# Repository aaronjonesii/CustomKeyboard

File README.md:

# CustomKeyboard
 Full Custom Mechanical Keyboard

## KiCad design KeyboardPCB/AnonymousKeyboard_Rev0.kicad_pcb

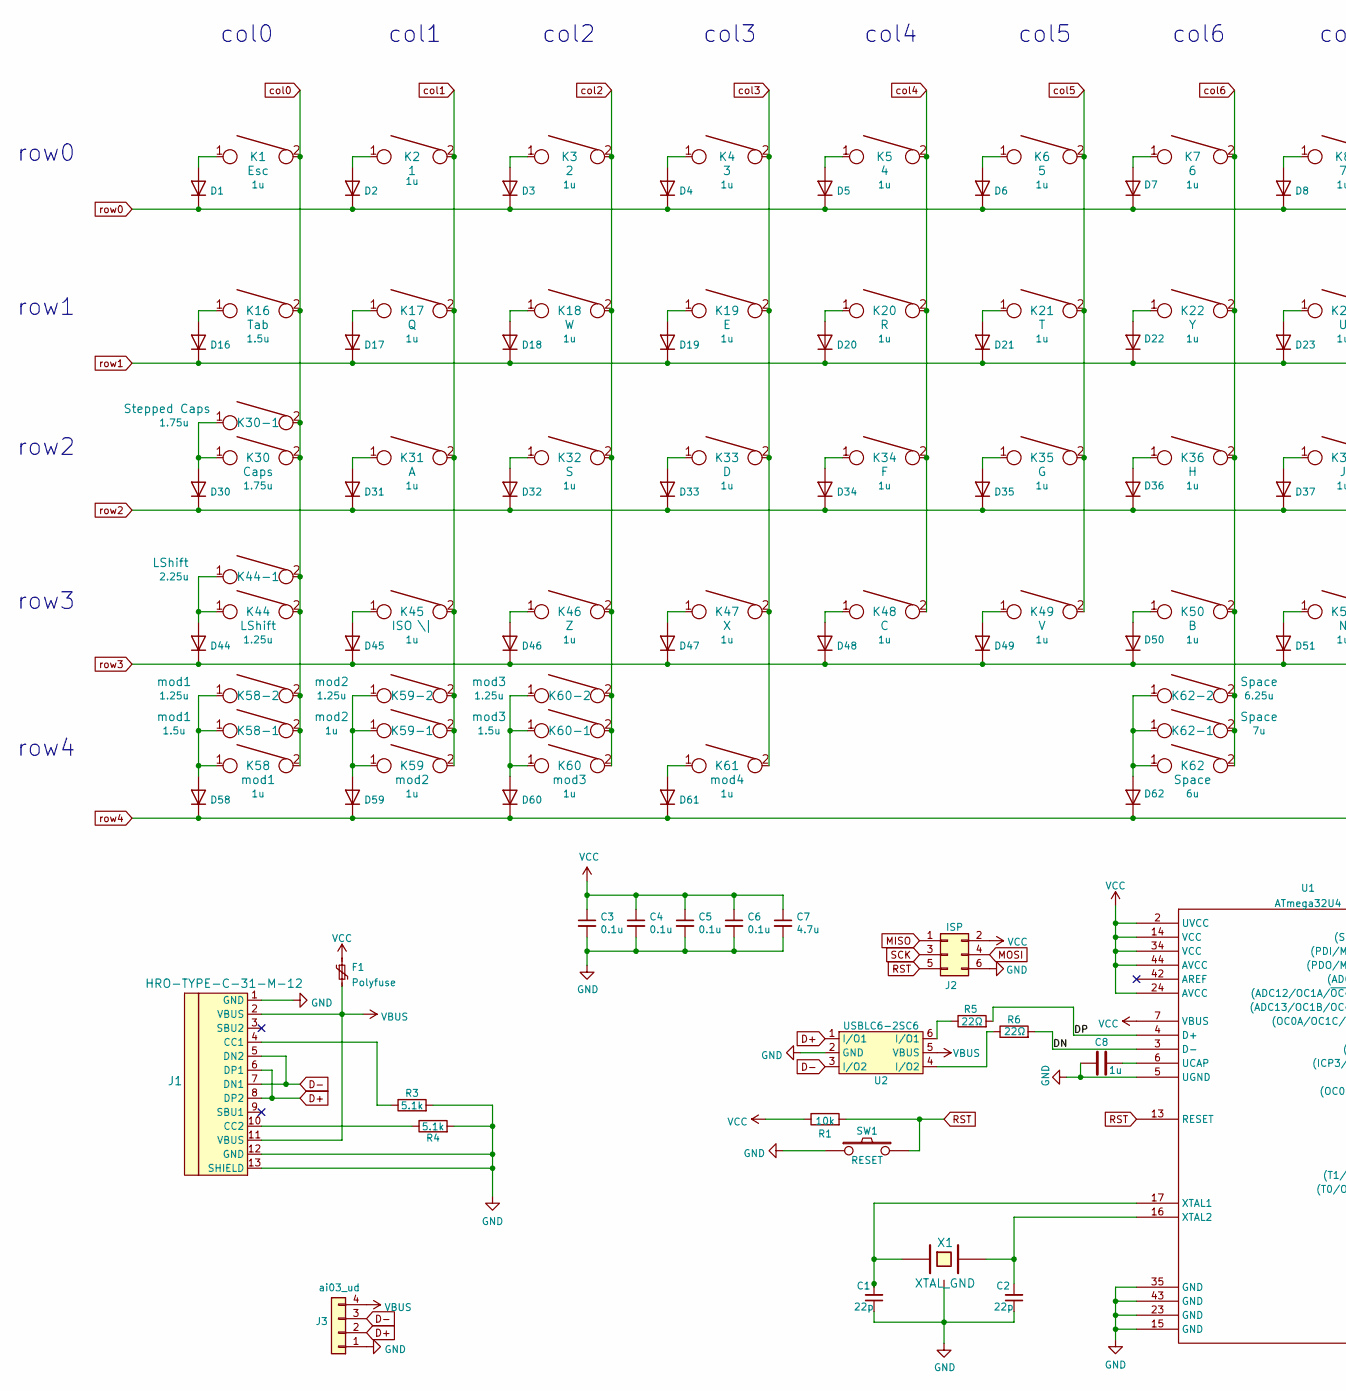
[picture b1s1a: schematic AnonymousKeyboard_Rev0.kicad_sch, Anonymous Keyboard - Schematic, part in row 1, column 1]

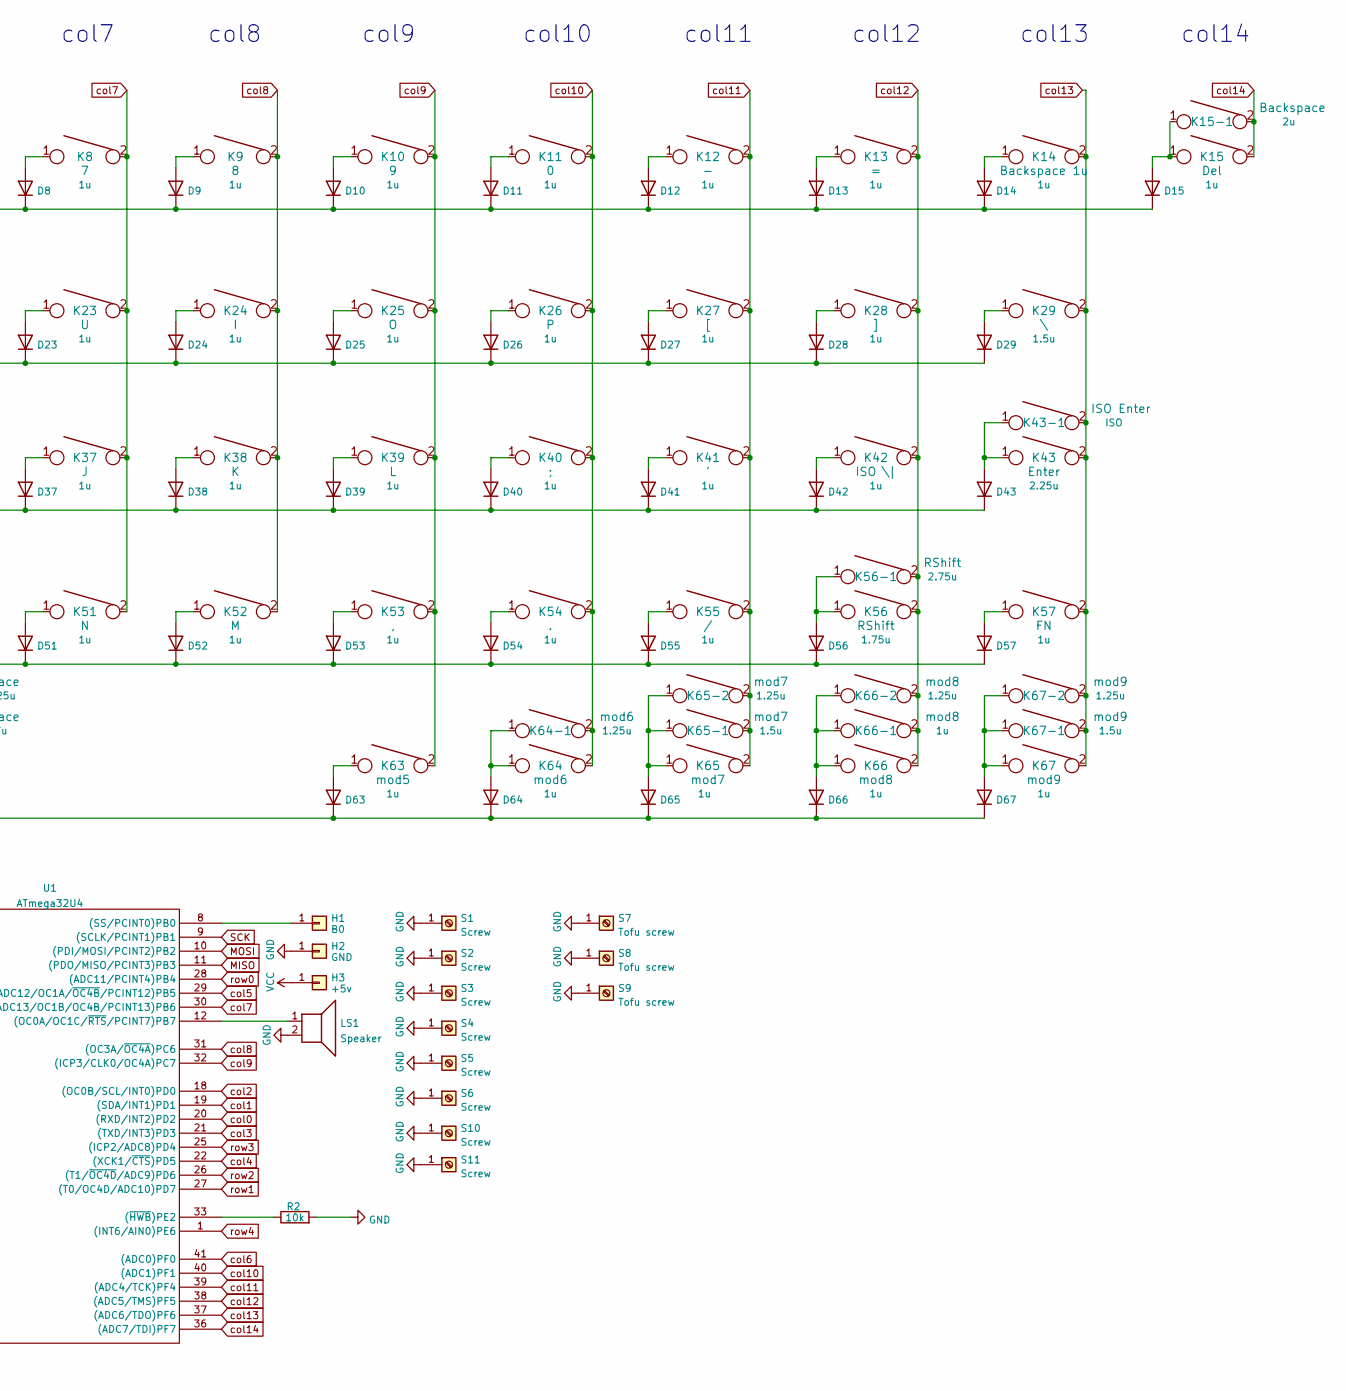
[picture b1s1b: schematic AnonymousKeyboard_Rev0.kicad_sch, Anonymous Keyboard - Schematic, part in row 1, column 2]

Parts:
C1, C2: 22p; C_0805_2012Metric_Pad1.18x1.45mm_HandSolder
C3, C4, C5, C6: 0.1u; C_0805_2012Metric_Pad1.18x1.45mm_HandSolder
C7: 4.7u; C_0805_2012Metric_Pad1.18x1.45mm_HandSolder
C8: 1u; C_0805_2012Metric_Pad1.18x1.45mm_HandSolder
D1, D2, D3, D4, D5, D6, D7, D8, D9, D10, D11, D12, D13, D14, D15, D16, D17, D18, D19, D20, D21, D22, D23, D24, D25, D26, D27, D28, D29, D30, D31, D32, D33, D34, D35, D36, D37, D38, D39, D40, D41, D42, D43, D44, D45, D46, D47, D48, D49, D50, D51, D52, D53, D54, D55, D56, D57, D58, D59, D60, D61, D62, D63, D64, D65, D66, D67: D; D_0805_2012Metric_Pad1.15x1.40mm_HandSolder
F1: Polyfuse; R_0805_2012Metric_Pad1.20x1.40mm_HandSolder
H1: B0; free_pin
H2: GND; free_pin
H3: +5v; free_pin
J1: HRO-TYPE-C-31-M-12; HRO-TYPE-C-31-M-12-Assembly
J2: ISP; AVR_ICSP_3x2
J3: ai03_ud; JST_SH_SM04B-SRSS-TB_1x04-1MP_P1.00mm_Horizontal
K1: Esc; MXOnly-1U-NoLED
K2: 1; MXOnly-1U-NoLED
K3: 2; MXOnly-1U-NoLED
K4: 3; MXOnly-1U-NoLED
K5: 4; MXOnly-1U-NoLED
K6: 5; MXOnly-1U-NoLED
K7: 6; MXOnly-1U-NoLED
K8: 7; MXOnly-1U-NoLED
K9: 8; MXOnly-1U-NoLED
K10: 9; MXOnly-1U-NoLED
K11: 0; MXOnly-1U-NoLED
K12: -; MXOnly-1U-NoLED
K13: =; MXOnly-1U-NoLED
K14: Backspace 1u; MXOnly-1U-NoLED
K15: Del; MXOnly-1U-NoLED
K15-1: Backspace; MXOnly-2U-NoLED
K16: Tab; MXOnly-1.5U-NoLED
K17: Q; MXOnly-1U-NoLED
K18: W; MXOnly-1U-NoLED
K19: E; MXOnly-1U-NoLED
K20: R; MXOnly-1U-NoLED
K21: T; MXOnly-1U-NoLED
K22: Y; MXOnly-1U-NoLED
K23: U; MXOnly-1U-NoLED
K24: I; MXOnly-1U-NoLED
K25: O; MXOnly-1U-NoLED
K26: P; MXOnly-1U-NoLED
K27: [; MXOnly-1U-NoLED
K28: ]; MXOnly-1U-NoLED
K29: \; MXOnly-1.5U-NoLED
K30: Caps; MXOnly-1.75U-NoLED
K30-1: Stepped Caps; MXOnly-1.25U-NoLED
K31: A; MXOnly-1U-NoLED
K32: S; MXOnly-1U-NoLED
K33: D; MXOnly-1U-NoLED
K34: F; MXOnly-1U-NoLED
K35: G; MXOnly-1U-NoLED
K36: H; MXOnly-1U-NoLED
K37: J; MXOnly-1U-NoLED
K38: K; MXOnly-1U-NoLED
K39: L; MXOnly-1U-NoLED
K40: ;; MXOnly-1U-NoLED
K41: '; MXOnly-1U-NoLED
K42, K45: ISO \|; MXOnly-1U-NoLED
K43: Enter; MXOnly-2.25U-NoLED
K43-1: ISO Enter; MXOnly-ISO-NoLED
K44: LShift; MXOnly-1.25U-NoLED
K44-1: LShift; MXOnly-2.25U-NoLED
K46: Z; MXOnly-1U-NoLED
K47: X; MXOnly-1U-NoLED
K48: C; MXOnly-1U-NoLED
K49: V; MXOnly-1U-NoLED
K50: B; MXOnly-1U-NoLED
K51: N; MXOnly-1U-NoLED
K52: M; MXOnly-1U-NoLED
K53: ,; MXOnly-1U-NoLED
K54: .; MXOnly-1U-NoLED
K55: /; MXOnly-1U-NoLED
K56: RShift; MXOnly-1.75U-NoLED
K56-1: RShift; MXOnly-2.75U-NoLED
K57: FN; MXOnly-1U-NoLED
K58: mod1; MXOnly-1U-NoLED
K58-1: mod1; MXOnly-1.5U-NoLED
K58-2: mod1; MXOnly-1.25U-NoLED
K59, K59-1: mod2; MXOnly-1U-NoLED
K59-2: mod2; MXOnly-1.25U-NoLED
K60: mod3; MXOnly-1U-NoLED
K60-1: mod3; MXOnly-1.5U-NoLED
K60-2: mod3; MXOnly-1.25U-NoLED
K61: mod4; MXOnly-1U-NoLED
K62: Space; MXOnly-6U-Centered-NoLED
K62-1: Space; MXOnly-7U-NoLED
K62-2: Space; MXOnly-6.25U-NoLED
K63: mod5; MXOnly-1U-NoLED
K64: mod6; MXOnly-1U-NoLED
K64-1: mod6; MXOnly-1.25U-NoLED
K65: mod7; MXOnly-1U-NoLED
K65-1: mod7; MXOnly-1.5U-NoLED
K65-2: mod7; MXOnly-1.25U-NoLED
K66, K66-1: mod8; MXOnly-1U-NoLED
K66-2: mod8; MXOnly-1.25U-NoLED
K67: mod9; MXOnly-1U-NoLED
K67-1: mod9; MXOnly-1.5U-NoLED
K67-2: mod9; MXOnly-1.25U-NoLED
LS1: Speaker; AST1109MLTRQ
R1, R2: 10k; R_0805
R3, R4: 5.1k; R_0805
R5, R6: 22Ω; R_0805
S1, S2, S4, S6, S10, S11: Screw; 5.5_5x2.5mm
S3, S5: Screw; 10x5_7x2.5mm
S7, S8, S9: Tofu screw; 5.5_5x2.5mm
SW1: RESET; ResetPins
U1: ATmega32U4; ATMEGA32U4-AU
U2: USBLC6-2SC6; TSOT-23-6_HandSoldering; Farnell 1295310
X1: XTAL_GND; FA-238

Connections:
/DN: R6.2, U1.3 (D-)
/DP: R5.2, U1.4 (D+)
D+: J1.6 (DP1), J1.8 (DP2), J3.2, U2.1 (I/O1)
D-: J1.5 (DN2), J1.7 (DN1), J3.3, U2.3 (I/O2)
GND: C1.1, C2.1, C3.2, C4.2, C5.2, C6.2, C7.2, C8.2, H2.1, J1.1 (GND), J1.12 (GND), J1.13 (SHIELD), J2.6, J3.1, LS1.2, R2.2, R3.2, R4.2, S1.1, S2.1, S3.1, S4.1, S5.1, S6.1, S7.1, S8.1, S9.1, S10.1, S11.1, SW1.1, U1.5 (UGND), U1.15 (GND), U1.23 (GND), U1.35 (GND), U1.43 (GND), U2.2 (GND), X1.3
MISO: J2.1, U1.11 ((PDO/MISO/PCINT3)PB3)
MOSI: J2.4, U1.10 ((PDI/MOSI/PCINT2)PB2)
unnamed: C1.2, U1.17 (XTAL1), X1.1
unnamed: C2.2, U1.16 (XTAL2), X1.2
unnamed: C8.1, U1.6 (UCAP)
unnamed: D1.2 (A), K1.1
unnamed: D2.2 (A), K2.1
unnamed: D3.2 (A), K3.1
unnamed: D4.2 (A), K4.1
unnamed: D5.2 (A), K5.1
unnamed: D6.2 (A), K6.1
unnamed: D7.2 (A), K7.1
unnamed: D8.2 (A), K8.1
unnamed: D9.2 (A), K9.1
unnamed: D10.2 (A), K10.1
unnamed: D11.2 (A), K11.1
unnamed: D12.2 (A), K12.1
unnamed: D13.2 (A), K13.1
unnamed: D14.2 (A), K14.1
unnamed: D15.2 (A), K15.1, K15-1.1
unnamed: D16.2 (A), K16.1
unnamed: D17.2 (A), K17.1
unnamed: D18.2 (A), K18.1
unnamed: D19.2 (A), K19.1
unnamed: D20.2 (A), K20.1
unnamed: D21.2 (A), K21.1
unnamed: D22.2 (A), K22.1
unnamed: D23.2 (A), K23.1
unnamed: D24.2 (A), K24.1
unnamed: D25.2 (A), K25.1
unnamed: D26.2 (A), K26.1
unnamed: D27.2 (A), K27.1
unnamed: D28.2 (A), K28.1
unnamed: D29.2 (A), K29.1
unnamed: D30.2 (A), K30.1, K30-1.1
unnamed: D31.2 (A), K31.1
unnamed: D32.2 (A), K32.1
unnamed: D33.2 (A), K33.1
unnamed: D34.2 (A), K34.1
unnamed: D35.2 (A), K35.1
unnamed: D36.2 (A), K36.1
unnamed: D37.2 (A), K37.1
unnamed: D38.2 (A), K38.1
unnamed: D39.2 (A), K39.1
unnamed: D40.2 (A), K40.1
unnamed: D41.2 (A), K41.1
unnamed: D42.2 (A), K42.1
unnamed: D43.2 (A), K43.1, K43-1.1
unnamed: D44.2 (A), K44.1, K44-1.1
unnamed: D45.2 (A), K45.1
unnamed: D46.2 (A), K46.1
unnamed: D47.2 (A), K47.1
unnamed: D48.2 (A), K48.1
unnamed: D49.2 (A), K49.1
unnamed: D50.2 (A), K50.1
unnamed: D51.2 (A), K51.1
unnamed: D52.2 (A), K52.1
unnamed: D53.2 (A), K53.1
unnamed: D54.2 (A), K54.1
unnamed: D55.2 (A), K55.1
unnamed: D56.2 (A), K56.1, K56-1.1
unnamed: D57.2 (A), K57.1
unnamed: D58.2 (A), K58.1, K58-1.1, K58-2.1
unnamed: D59.2 (A), K59.1, K59-1.1, K59-2.1
unnamed: D60.2 (A), K60.1, K60-1.1, K60-2.1
unnamed: D61.2 (A), K61.1
unnamed: D62.2 (A), K62.1, K62-1.1, K62-2.1
unnamed: D63.2 (A), K63.1
unnamed: D64.2 (A), K64.1, K64-1.1
unnamed: D65.2 (A), K65.1, K65-1.1, K65-2.1
unnamed: D66.2 (A), K66.1, K66-1.1, K66-2.1
unnamed: D67.2 (A), K67.1, K67-1.1, K67-2.1
unnamed: H1.1, U1.8 ((SS/PCINT0)PB0)
unnamed: J1.4 (CC1), R3.1
unnamed: J1.10 (CC2), R4.1
unnamed: LS1.1, U1.12 ((OC0A/OC1C/~RTS/PCINT7)PB7)
unnamed: R2.1, U1.33 ((~HWB)PE2)
unnamed: R5.1, U2.6 (I/O1)
unnamed: R6.1, U2.4 (I/O2)
RST: J2.5, R1.2, SW1.2, U1.13 (RESET)
SCK: J2.3, U1.9 ((SCLK/PCINT1)PB1)
VBUS: F1.2, J1.2 (VBUS), J1.11 (VBUS), J3.4, U2.5 (VBUS)
VCC: C3.1, C4.1, C5.1, C6.1, C7.1, F1.1, H3.1, J2.2, R1.1, U1.2 (UVCC), U1.7 (VBUS), U1.14 (VCC), U1.24 (AVCC), U1.34 (VCC), U1.44 (AVCC)
col0: K1.2, K16.2, K30.2, K30-1.2, K44.2, K44-1.2, K58.2, K58-1.2, K58-2.2, U1.20 ((RXD/INT2)PD2)
col1: K2.2, K17.2, K31.2, K45.2, K59.2, K59-1.2, K59-2.2, U1.19 ((SDA/INT1)PD1)
col2: K3.2, K18.2, K32.2, K46.2, K60.2, K60-1.2, K60-2.2, U1.18 ((OC0B/SCL/INT0)PD0)
col3: K4.2, K19.2, K33.2, K47.2, K61.2, U1.21 ((TXD/INT3)PD3)
col4: K5.2, K20.2, K34.2, K48.2, U1.22 ((XCK1/~CTS)PD5)
col5: K6.2, K21.2, K35.2, K49.2, U1.29 ((ADC12/OC1A/~OC4B/PCINT12)PB5)
col6: K7.2, K22.2, K36.2, K50.2, K62.2, K62-1.2, K62-2.2, U1.41 ((ADC0)PF0)
col7: K8.2, K23.2, K37.2, K51.2, U1.30 ((ADC13/OC1B/OC4B/PCINT13)PB6)
col8: K9.2, K24.2, K38.2, K52.2, U1.31 ((OC3A/~OC4A)PC6)
col9: K10.2, K25.2, K39.2, K53.2, K63.2, U1.32 ((ICP3/CLK0/OC4A)PC7)
col10: K11.2, K26.2, K40.2, K54.2, K64.2, K64-1.2, U1.40 ((ADC1)PF1)
col11: K12.2, K27.2, K41.2, K55.2, K65.2, K65-1.2, K65-2.2, U1.39 ((ADC4/TCK)PF4)
col12: K13.2, K28.2, K42.2, K56.2, K56-1.2, K66.2, K66-1.2, K66-2.2, U1.38 ((ADC5/TMS)PF5)
col13: K14.2, K29.2, K43.2, K43-1.2, K57.2, K67.2, K67-1.2, K67-2.2, U1.37 ((ADC6/TDO)PF6)
col14: K15.2, K15-1.2, U1.36 ((ADC7/TDI)PF7)
row0: D1.1 (K), D2.1 (K), D3.1 (K), D4.1 (K), D5.1 (K), D6.1 (K), D7.1 (K), D8.1 (K), D9.1 (K), D10.1 (K), D11.1 (K), D12.1 (K), D13.1 (K), D14.1 (K), D15.1 (K), U1.28 ((ADC11/PCINT4)PB4)
row1: D16.1 (K), D17.1 (K), D18.1 (K), D19.1 (K), D20.1 (K), D21.1 (K), D22.1 (K), D23.1 (K), D24.1 (K), D25.1 (K), D26.1 (K), D27.1 (K), D28.1 (K), D29.1 (K), U1.27 ((T0/OC4D/ADC10)PD7)
row2: D30.1 (K), D31.1 (K), D32.1 (K), D33.1 (K), D34.1 (K), D35.1 (K), D36.1 (K), D37.1 (K), D38.1 (K), D39.1 (K), D40.1 (K), D41.1 (K), D42.1 (K), D43.1 (K), U1.26 ((T1/~OC4D/ADC9)PD6)
row3: D44.1 (K), D45.1 (K), D46.1 (K), D47.1 (K), D48.1 (K), D49.1 (K), D50.1 (K), D51.1 (K), D52.1 (K), D53.1 (K), D54.1 (K), D55.1 (K), D56.1 (K), D57.1 (K), U1.25 ((ICP2/ADC8)PD4)
row4: D58.1 (K), D59.1 (K), D60.1 (K), D61.1 (K), D62.1 (K), D63.1 (K), D64.1 (K), D65.1 (K), D66.1 (K), D67.1 (K), U1.1 ((INT6/AIN0)PE6)

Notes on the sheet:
row0
row1
row2
row3
row4
col0
col1
col2
col3
col4
col5
col6
col7
col8
col9
col10
col11
col12
col13
col14

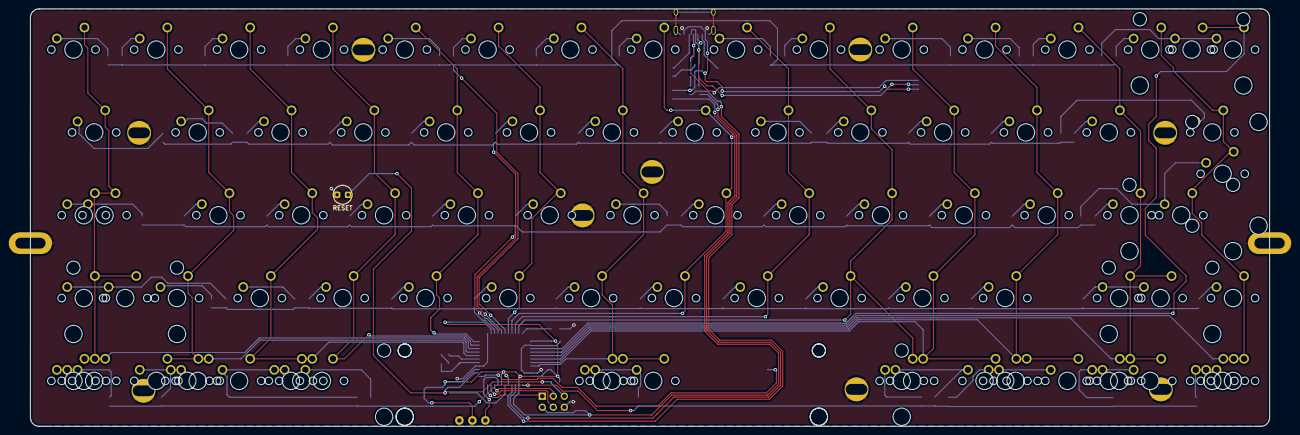
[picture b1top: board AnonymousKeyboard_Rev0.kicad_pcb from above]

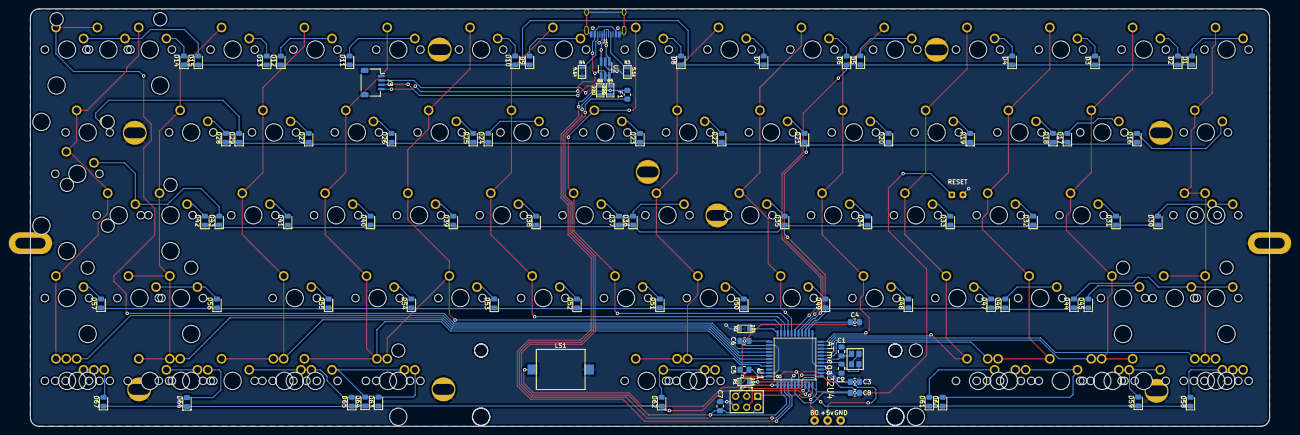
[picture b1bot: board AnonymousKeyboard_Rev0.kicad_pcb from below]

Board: 2 copper layers, 285.0 x 96.0 mm, 191 parts (89 on the bottom side), 108 nets.

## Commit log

2021-08-27 Chore: Initial Commit
